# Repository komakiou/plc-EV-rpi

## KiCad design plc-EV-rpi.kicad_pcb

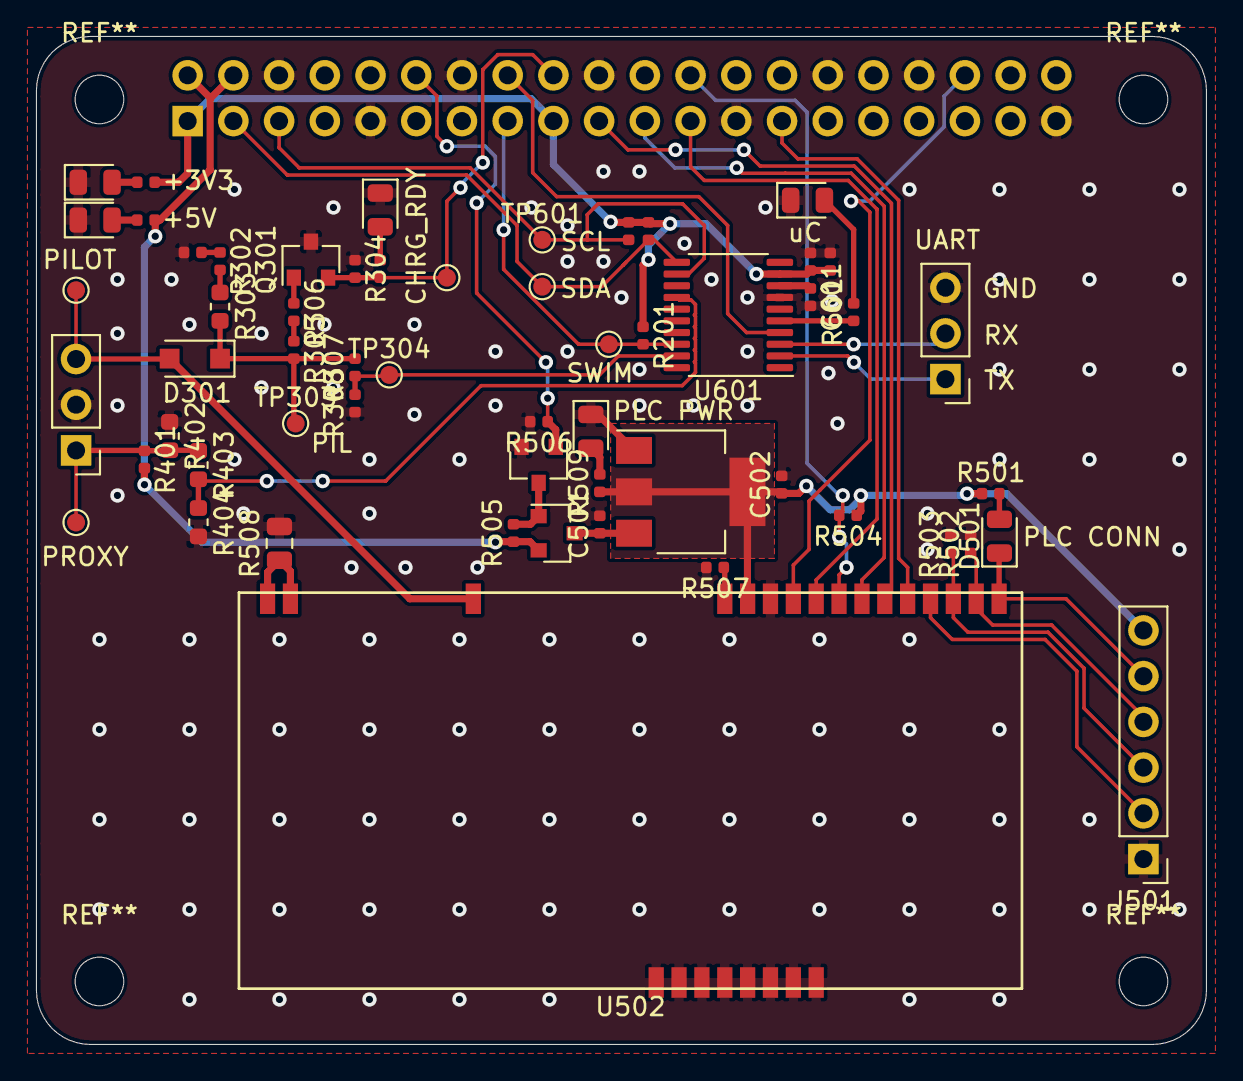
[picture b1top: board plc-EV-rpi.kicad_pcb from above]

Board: 2 copper layers, 65.0 x 56.0 mm, 58 parts (1 on the bottom side), 43 nets.

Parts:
C501, C502, C602: 1u; C_0402_1005Metric
C601, C603: 100n; C_0402_1005Metric
D201, D202, D203, D501, D502, D601: LED_0805; LED_0805_2012Metric
D301: SM4007PL; D_SOD-123F
J101, J601: Conn_01x03; PinHeader_1x03_P2.54mm_Vertical
J201: Raspberry_Pi_2_3; PinSocket_2x20_P2.54mm_Vertical
J501: GPIO; PinHeader_1x06_P2.54mm_Vertical
Q301, Q501: AO3400A; SOT-23
Q502: AO3401A; SOT-23
R201, R206, R207, R502, R503, R504: 2k2; R_0402_1005Metric
R202, R203, R301, R302, R509, R601: 200; R_0402_1005Metric
R205: 300; R_0402_1005Metric
R303, R402: 2k7; R_0603_1608Metric
R304, R505, R506, R507: 10k; R_0402_1005Metric
R305: 1k2; R_0402_1005Metric
R306: 100; R_0402_1005Metric
R307: 47k; R_0402_1005Metric
R308: 18k; R_0402_1005Metric
R401: 330; R_0402_1005Metric
R403: 30k; R_0603_1608Metric
R404: 82k; R_0603_1608Metric
R501: 1k; R_0402_1005Metric
R508: 0; R_0805_2012Metric
TP301, TP302, TP303, TP304, TP401, TP601, TP602, TP603: TestPoint; TestPoint_Pad_D1.0mm
U501: AMS1117-3.3; SOT-223-3_TabPin2
U502: PLC_Stamp_mini_2
U601: STM8S003F3P; TSSOP-20_4.4x6.5mm_P0.65mm

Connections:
+3V3: C602.1, C603.1, J201.1, J201.17, R201.1, R203.1, R206.1, R207.1, U601.9
+5V: J201.2, J201.4, Q502.2, R205.1, R401.2, R505.1
/PILOT: D301.2, J101.3, TP301.1, U502.15
/PLC Interface/CLK: J201.23, U502.9
/PLC Interface/CS: J201.24, R504.2, U502.8
/PLC Interface/ENABLE: J201.12, Q501.1, R506.1
/PLC Interface/GPIO_0: D501.1, J501.5, U502.1
/PLC Interface/GPIO_1: J501.4, R502.1, U502.2
/PLC Interface/GPIO_2: J501.3, R503.1, U502.3
/PLC Interface/GPIO_3: J501.2, U502.4
/PLC Interface/INT: J201.36, U502.10
/PLC Interface/MISO: J201.21, U502.7
/PLC Interface/MOSI: J201.19, U502.6
/PLC Interface/VDD: C502.1, J501.6, R501.1, R504.1, R509.1, U501.2, U502.12
/PROXY: J101.1, R401.1, R402.2, R403.1, TP401.1
/Pilot EV/CHARDE_RDY: J201.18, Q301.2, R202.1, R304.2, TP302.1
/RaspberryPi/PLC_RESET: J201.27, U502.5
/RaspberryPi/SCL: J201.5, R207.2, TP601.1, U601.12
/RaspberryPi/SDA: J201.3, R206.2, TP602.1, U601.11
/RaspberryPi/STM8_SWIM: J201.15, R201.2, TP603.1, U601.18
/STM8/AIN2: R403.2, R404.1, U601.14
/STM8/AIN3: R307.1, R308.2, TP304.1, U601.19
/STM8/NRST: J201.16, U601.4
/STM8/UART_RX: J601.2, U601.3
/STM8/UART_TX: J601.1, U601.2
GND: C501.2, C502.2, C601.2, C602.2, C603.2, D201.1, D202.1, D203.1, D502.1, D601.1, J101.2, J201.6, J201.9, J201.14, J201.20, J201.25, J201.30, J201.34, J201.39, J501.1, J601.3, Q301.3, Q501.2, R301.1, R304.1, R308.1, R402.1, R404.2, R502.2, R503.2, R506.2, R507.2, R508.2, U501.1, U502.11, U502.18, U502.19, U502.20, U502.21, U502.22, U502.23, U502.24, U502.25, U601.7
unnamed: C501.1, Q502.3, U501.3
unnamed: C601.1, U601.8
unnamed: D201.2, R202.2
unnamed: D202.2, R203.2
unnamed: D203.2, R205.2
unnamed: D301.1, R303.2, R305.2, R307.2, TP303.1
unnamed: D501.2, R501.2
unnamed: D502.2, R509.2
unnamed: D601.2, R601.2
unnamed: Q301.1, R306.1
unnamed: Q501.3, Q502.1, R505.2
unnamed: R301.2, R302.1
unnamed: R302.2, R303.1
unnamed: R305.1, R306.2
unnamed: R507.1, U502.13
unnamed: R508.1, U502.16, U502.17
unnamed: R601.1, U601.5

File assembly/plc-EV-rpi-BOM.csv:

Comment,Designator,Footprint,LCSC
1u,"C501,C502,C602",Capacitor_SMD:C_0402_1005Metric,C52923
100n,"C601,C603",Capacitor_SMD:C_0402_1005Metric,C1525
LED_0805,"D203,D202,D201,D501,D502,D601",LED_SMD:LED_0805_2012Metric,C2297
SM4007PL,D301,Diode_SMD:D_SOD-123F,C64898
AO3400A,"Q301,Q501",Package_TO_SOT_SMD:SOT-23,C20917
AO3401A,Q502,Package_TO_SOT_SMD:SOT-23,C15127
200,"R203,R202,R302,R301,R509,R601",Resistor_SMD:R_0402_1005Metric,C25087
300,R205,Resistor_SMD:R_0402_1005Metric,C25102
2k2,"R206,R207,R201,R502,R503,R504",Resistor_SMD:R_0402_1005Metric,C25879
2k7,"R303,R402",Resistor_SMD:R_0603_1608Metric,C13167
10k,"R304,R507,R505,R506",Resistor_SMD:R_0402_1005Metric,C25744
1k2,R305,Resistor_SMD:R_0402_1005Metric,C25862
100,R306,Resistor_SMD:R_0402_1005Metric, C25076
47k,R307,Resistor_SMD:R_0402_1005Metric,C25792
18k,R308,Resistor_SMD:R_0402_1005Metric,C25762
330,R401,Resistor_SMD:R_0402_1005Metric,C25104
30k,R403,Resistor_SMD:R_0603_1608Metric,C22984
82k,R404,Resistor_SMD:R_0603_1608Metric,C23254
1k,R501,Resistor_SMD:R_0402_1005Metric,C11702
0,R508,Resistor_SMD:R_0805_2012Metric,C17477
AMS1117-3.3,U501,Package_TO_SOT_SMD:SOT-223-3_TabPin2,C6186
STM8S003F3P,U601,Package_SO:TSSOP-20_4.4x6.5mm_P0.65mm,C52717

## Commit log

2020-06-25 Intitial checkin
    Kicad Raspberry Pi Hat for PLC CCS charging interface
2020-06-25 Submitted for production trail at jlcpcb
2020-06-25 first production trial run
